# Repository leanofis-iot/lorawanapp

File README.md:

# mobileapp

## Run

In the project directory, run the [Tabris CLI](https://www.npmjs.com/package/tabris-cli) command:

```
tabris serve
```

This will start a JavaScript app code server at a free port and print its URL to the console.

The JavaScript app code can be [side-loaded](https://tabrisjs.com/documentation/2.0/developer-app.html#the-developer-console) in the [developer app](https://tabrisjs.com/documentation/2.0/developer-app.html) if the default config.xml was not changed. Otherwise, the JavaScript app code must be side-loaded in a [debug build](https://tabrisjs.com/documentation/2.0/build.html#building-a-tabrisjs-app) of this app.

## Build

The app can be built using the online build service at [tabrisjs.com](https://tabrisjs.com) or locally using [Tabris.js CLI](https://www.npmjs.com/package/tabris-cli).

See [Building a Tabris.js App](https://tabrisjs.com/documentation/2.0/build.html) for more information.

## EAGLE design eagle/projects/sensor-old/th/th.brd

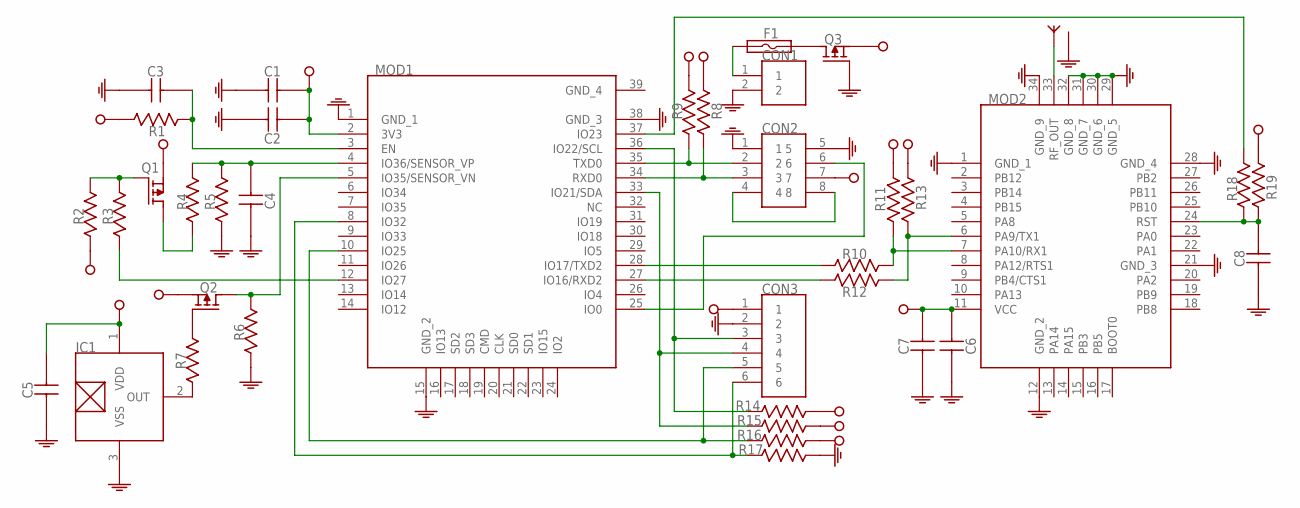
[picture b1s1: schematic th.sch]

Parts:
ANT1: SMA-RF
C1, C6: CAPACITOR-0805; 0805
C2, C3, C4, C5, C7, C8: CAPACITOR-0603; 0603
CON1: JST-PH-2-2.0MM
CON2: HEADER-8P-2R-DIP-2_0MM
CON3: CON-6P-3_81-PLUG
F1: FUSE-0805; 0805
IC1: S-5712-SOT23-3; SOT23-3
MOD1: ESP32-WROOM-32D
MOD2: RAK811
Q1, Q2, Q3: P-MOSFET; SOT23-3
R1, R2, R3, R4, R5, R6, R7, R8, R9, R10, R11, R12, R13, R14, R15, R16, R17, R18, R19: RESISTOR-0603; 0603

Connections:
GND: ANT1.2 (GND), ANT1.3 (GND), ANT1.4 (GND), ANT1.5 (GND), C1.1, C2.1, C3.1, C4.1, C5.1, C6.1, C7.1, C8.1, CON1.2, CON2.1, CON2.5, CON3.2, IC1.3 (VSS), MOD1.1 (GND_1), MOD1.15 (GND_2), MOD1.38 (GND_3), MOD2.1 (GND_1), MOD2.12 (GND_2), MOD2.21 (GND_3), MOD2.28 (GND_4), MOD2.29 (GND_5), MOD2.30 (GND_6), MOD2.31 (GND_7), MOD2.32 (GND_8), MOD2.34 (GND_9), Q3.1 (G), R5.1, R6.1, R17.2
GND_4: MOD1.39 (GND_4)
unnamed: C3.2, MOD1.3 (EN), R1.2
unnamed: IC1.2 (OUT), R7.1
unnamed: MOD2.6 (PA9/TX1), R12.2, R13.2
unnamed: MOD2.7 (PA10/RX1), R10.2, R11.2
unnamed: Q2.1 (G), R7.2
unnamed: MOD1.28 (IO17/TXD2), R10.1
unnamed: MOD1.27 (IO16/RXD2), R12.1
unnamed: CON2.2, MOD1.35 (TXD0), R9.1
unnamed: CON2.3, MOD1.34 (RXD0), R8.1
unnamed: CON2.4, CON2.8
unnamed: CON2.6, MOD1.25 (IO0)
unnamed: CON3.4, MOD1.33 (IO21/SDA), R15.1
unnamed: CON3.3, MOD1.36 (IO22/SCL), R14.1
unnamed: CON3.5, MOD1.10 (IO25), R16.1
unnamed: CON3.6, MOD1.8 (IO32), R17.1
unnamed: Q1.3 (D), R4.1
unnamed: C4.2, MOD1.4 (IO36/SENSOR_VP), R4.2, R5.2
unnamed: Q1.1 (G), R2.2, R3.2
unnamed: MOD1.12 (IO27), R3.1
unnamed: MOD1.5 (IO35/SENSOR_VN), Q2.3 (D), R6.2
unnamed: ANT1.1 (ANT), MOD2.33 (RF_OUT)
unnamed: C8.2, MOD2.24 (RST), R18.1, R19.1
unnamed: MOD1.37 (IO23), R18.2
unnamed: F1.2, Q3.3 (D)
unnamed: CON1.1, F1.1
VCC: C1.2, C2.2, C5.2, C6.2, C7.2, CON2.7, CON3.1, IC1.1 (VDD), MOD1.2 (3V3), MOD2.11 (VCC), Q1.2 (S), Q2.2 (S), Q3.2 (S), R1.1, R2.1, R8.2, R9.2, R11.1, R13.1, R14.2, R15.2, R16.2, R19.2

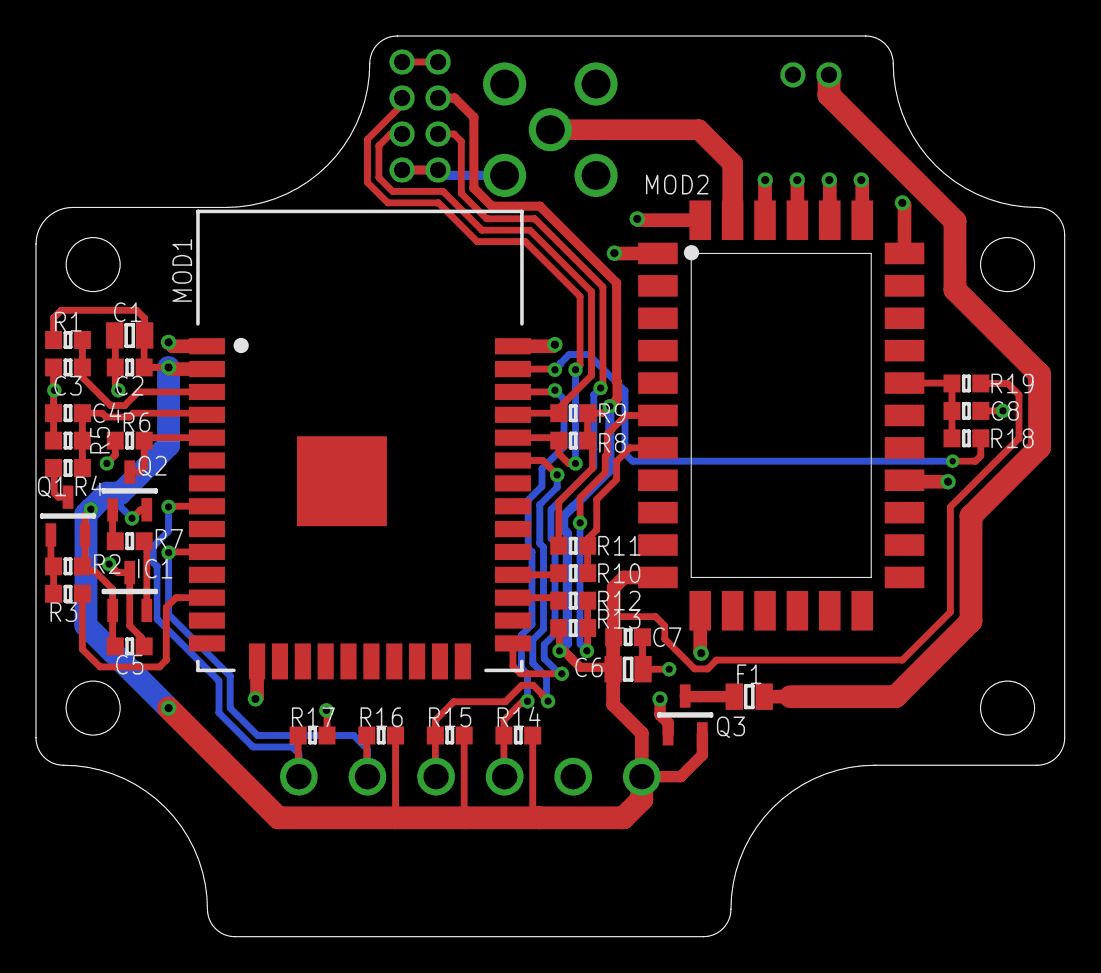
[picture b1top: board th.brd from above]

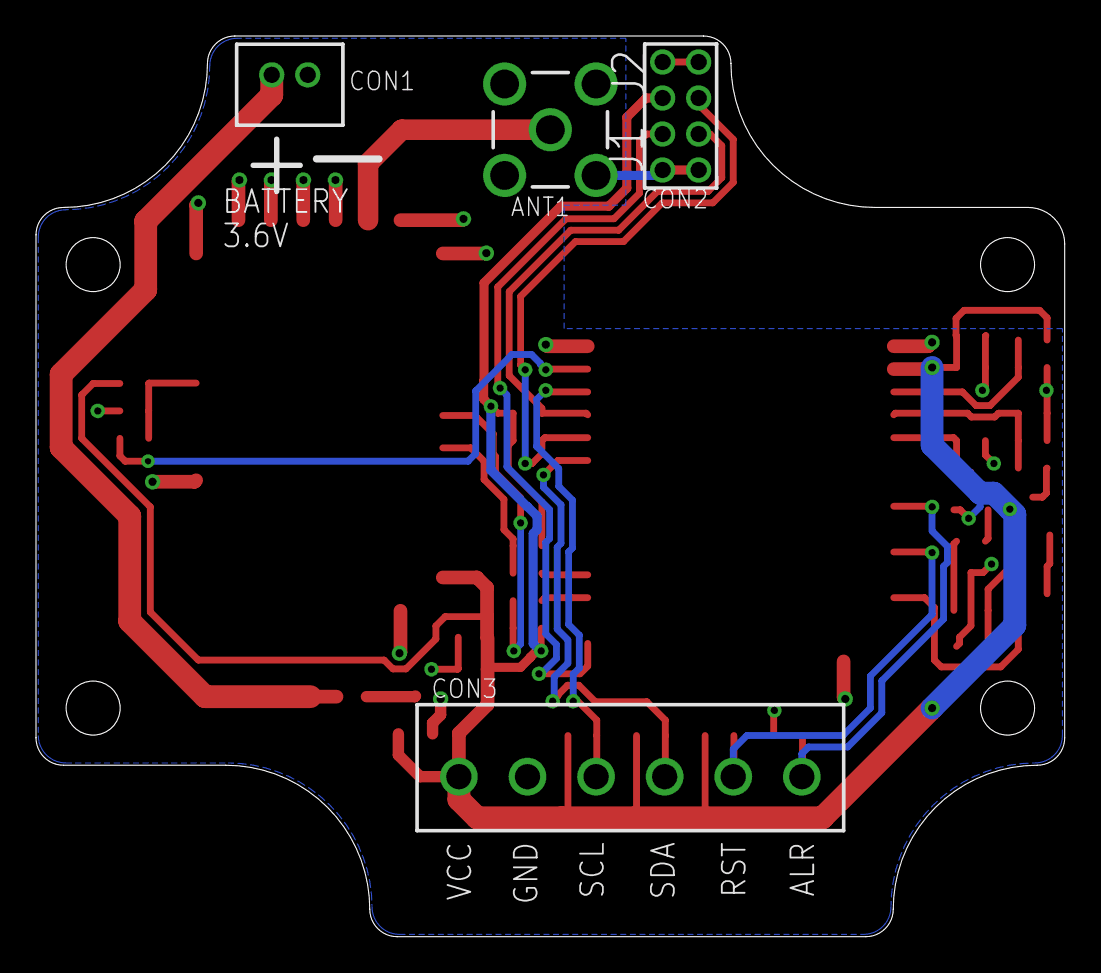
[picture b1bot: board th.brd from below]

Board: 2 copper layers, 57.1 x 50.0 mm, 38 parts (4 on the bottom side), 27 nets.

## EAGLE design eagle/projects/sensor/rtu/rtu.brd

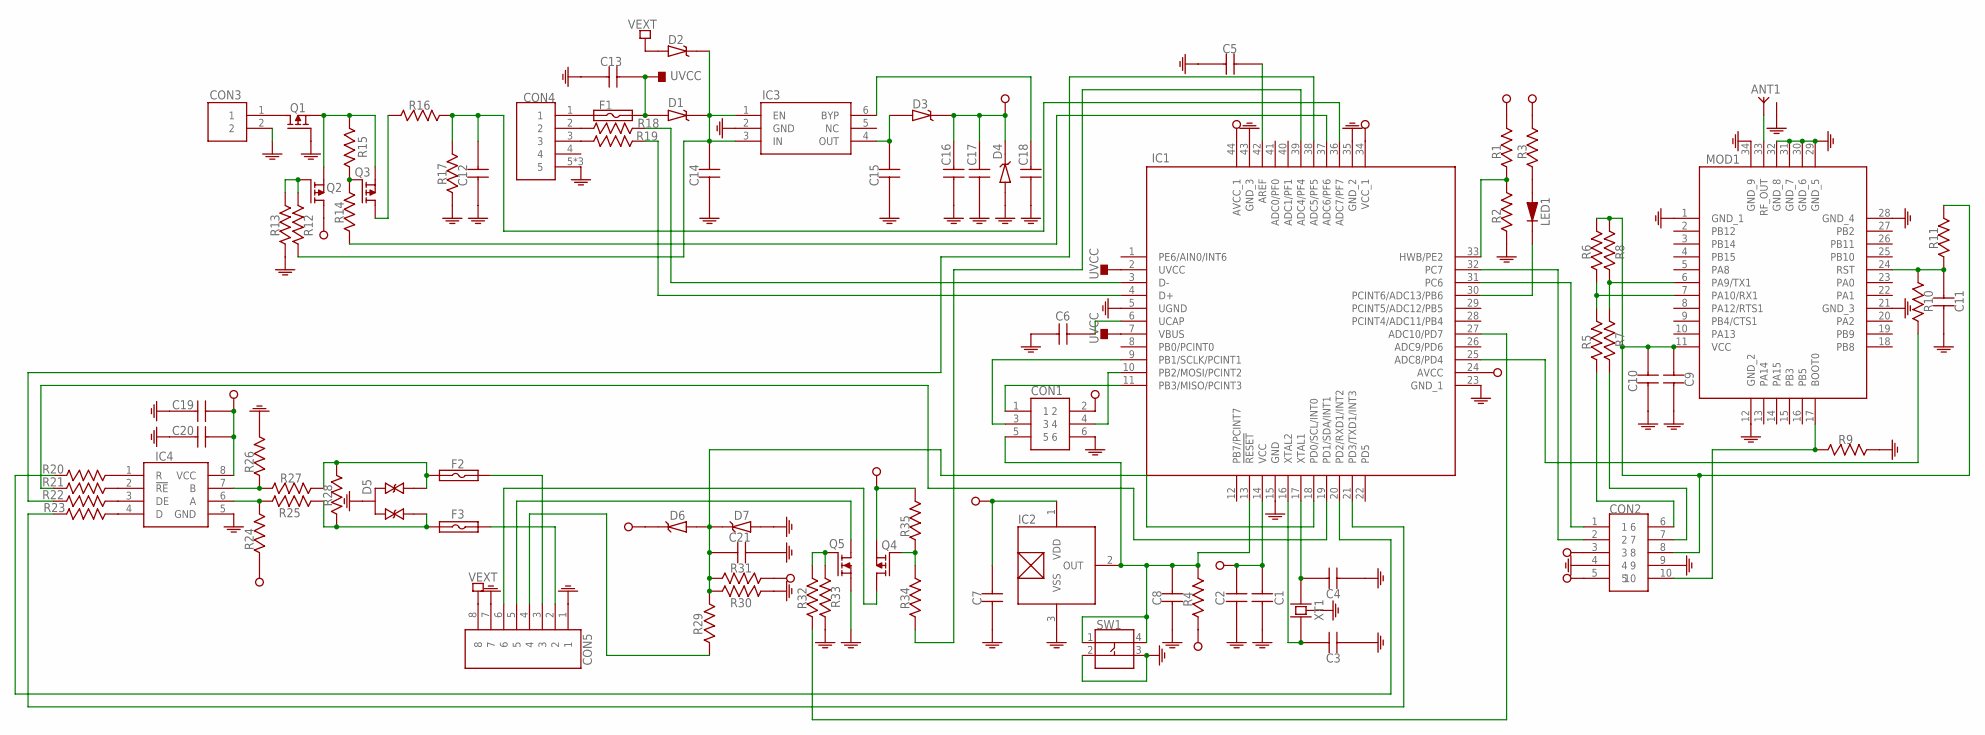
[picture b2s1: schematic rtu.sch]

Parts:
ANT1: SMA-RF
C1, C2, C3, C4, C5, C6, C7, C8, C9, C10, C11, C12, C13, C16, C17, C18, C19, C20, C21: CAPACITOR-0603; 0603
C14, C15: CAPACITOR-0805; 0805
CON1: ISP
CON2: HEADER-10P-2R-DIP-2_54MM
CON3: JST-PH-2-2.0MM
CON4: USB-MICRO-DIP-VER
CON5: CON-3_50MM-8P-1985250
D1, D2, D3: DIODE-SCHOTTKY; SOD123-DIODE
D4, D6, D7: ZENER-SOD123; SOD123-DIODE
D5: TVS-DIODE-3P; SOT23-3
F1: FUSE-0805; 0805
F2, F3: FUSE-1206; 1206
IC1: ATMEGA32U4-MU; QFN-44
IC2: S-5712-SOT23-3; SOT23-3
IC3: MIC5219-VDFN-6; VDFN-6
IC4: SN65HVD72DRB; VSON-8
LED1: LED-0603
MOD1: RAK811
Q1, Q2, Q3, Q4: P-MOSFET; SOT23-3
Q5: N-MOSFET; SOT23-3
R1, R2, R3, R4, R5, R6, R7, R8, R9, R10, R11, R12, R13, R14, R15, R16, R17, R18, R19, R20, R21, R22, R23, R24, R26, R32, R33, R34, R35: RESISTOR-0603; 0603
R25, R27: RESISTOR-0805; 0805
R28, R29, R30, R31: RESISTOR-JMP-2_54MM; HEADER-2P-DIP-2_54MM
SW1: BUTTON-4P-SMD-5X5
XT1: CRYSTAL-5032-4P

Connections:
GND: ANT1.2 (GND), ANT1.3 (GND), ANT1.4 (GND), ANT1.5 (GND), C1.1, C2.1, C3.1, C4.1, C5.1, C6.1, C7.1, C8.1, C9.1, C10.1, C11.1, C12.1, C13.1, C14.1, C15.1, C16.1, C17.1, C18.1, C19.1, C20.1, C21.2, CON1.6, CON2.4, CON2.9, CON3.2, CON4.5, CON4.6 (5), CON4.7 (5), CON5.1, CON5.7, D4.2 (A), D5.3, D7.2 (A), IC1.5 (UGND), IC1.15 (GND), IC1.23 (GND_1), IC1.35 (GND_2), IC1.43 (GND_3), IC2.3 (VSS), IC3.2 (GND), IC4.5 (GND), MOD1.1 (GND_1), MOD1.12 (GND_2), MOD1.21 (GND_3), MOD1.28 (GND_4), MOD1.29 (GND_5), MOD1.30 (GND_6), MOD1.31 (GND_7), MOD1.32 (GND_8), MOD1.34 (GND_9), Q1.1 (G), Q5.2 (S), R2.1, R9.2, R13.1, R17.1, R26.2, R30.1, R33.1, SW1.2, SW1.3, XT1.2 (GND), XT1.4 (GND)
unnamed: IC1.19 (PD1/SDA/INT1), R21.1
unnamed: C11.2, MOD1.24 (RST), R10.1, R11.1
unnamed: CON1.1, IC1.11 (PB3/MISO/PCINT3)
unnamed: ANT1.1 (ANT), MOD1.33 (RF_OUT)
unnamed: CON5.6, Q4.3 (D)
unnamed: MOD1.7 (PA10/RX1), R5.2, R6.1
unnamed: MOD1.6 (PA9/TX1), R7.2, R8.1
unnamed: IC1.27 (ADC10/PD7), R32.1
unnamed: CON1.4, IC1.10 (PB2/MOSI/PCINT2)
unnamed: C3.2, IC1.16 (XTAL2), XT1.1
unnamed: CON5.4, R29.1
unnamed: C4.2, IC1.17 (XTAL1), XT1.3 (2)
unnamed: C9.2, C10.2, CON2.8, MOD1.11 (VCC), R6.2, R8.2, R11.2
unnamed: CON2.7, R7.1
unnamed: Q5.1 (G), R32.2, R33.2
unnamed: IC1.25 (ADC8/PD4), R10.2
unnamed: D5.1, F3.1, R25.2, R28.2
unnamed: IC1.30 (PCINT6/ADC13/PB6), LED1.1 (K)
unnamed: CON2.1, IC1.31 (PC6)
unnamed: C21.1, D6.2 (A), D7.1 (K), IC1.18 (PD0/SCL/INT0), R29.2, R30.2, R31.2
unnamed: CON2.2, IC1.32 (PC7)
unnamed: IC1.20 (PD2/RXD1/INT2), R20.1
unnamed: IC1.21 (PD3/TXD1/INT3), R23.1
unnamed: IC4.7 (B), R26.1, R27.1
unnamed: IC4.6 (A), R24.2, R25.1
unnamed: CON5.3, F2.2
unnamed: CON5.5, Q5.3 (D)
unnamed: D5.2, F2.1, R27.2, R28.1
unnamed: C5.2, IC1.42 (AREF)
unnamed: Q3.1 (G), R14.2, R15.2
unnamed: CON4.1, F1.1
unnamed: C6.2, IC1.6 (UCAP)
unnamed: LED1.2 (A), R3.1
unnamed: C12.2, IC1.36 (ADC7/PF7), R16.2, R17.2
unnamed: C18.2, IC3.6 (BYP)
unnamed: C14.2, D1.1 (K), D2.1 (K), IC3.1 (EN), IC3.3 (IN), R12.1
unnamed: C15.2, D3.2 (A), IC3.4 (OUT)
unnamed: CON4.2, R18.1
unnamed: CON4.3, R19.1
unnamed: IC1.3 (D-), R18.2
unnamed: IC1.4 (D+), R19.2
unnamed: CON1.3, IC1.9 (PB1/SCLK/PCINT1)
unnamed: Q4.1 (G), R34.2, R35.1
unnamed: IC1.37 (ADC6/PF6), R14.1
unnamed: IC4.1 (R), R20.2
unnamed: IC1.38 (ADC5/PF5), R22.1
unnamed: IC1.39 (ADC4/PF4), R34.1
unnamed: IC4.2 (!RE), R21.2
unnamed: Q2.1 (G), R12.2, R13.2
unnamed: IC4.3 (DE), R22.2
unnamed: CON3.1, Q1.3 (D)
unnamed: IC4.4 (D), R23.2
unnamed: CON5.2, F3.2
unnamed: Q1.2 (S), Q2.2 (S), Q3.2 (S), R15.1
unnamed: Q3.3 (D), R16.1
unnamed: CON2.6, R5.1
unnamed: IC1.33 (HWB/PE2), R1.1, R2.2
unnamed: CON2.10, MOD1.17 (BOOT0), R9.1
unnamed: C8.2, CON1.5, IC1.13 (!RESET), IC2.2 (OUT), R4.2, SW1.1, SW1.4
UVCC: C13.2, D1.2 (A), F1.2, IC1.2 (UVCC), IC1.7 (VBUS)
VCC: C1.2, C2.2, C7.2, C16.2, C17.2, C19.2, C20.2, CON1.2, CON2.3, CON2.5, D3.1 (K), D4.1 (K), D6.1 (K), IC1.14 (VCC), IC1.24 (AVCC), IC1.34 (VCC_1), IC1.44 (AVCC_1), IC2.1 (VDD), IC4.8 (VCC), Q2.3 (D), Q4.2 (S), R1.2, R3.2, R4.1, R24.1, R31.1, R35.2
VEXT: CON5.8, D2.2 (A)

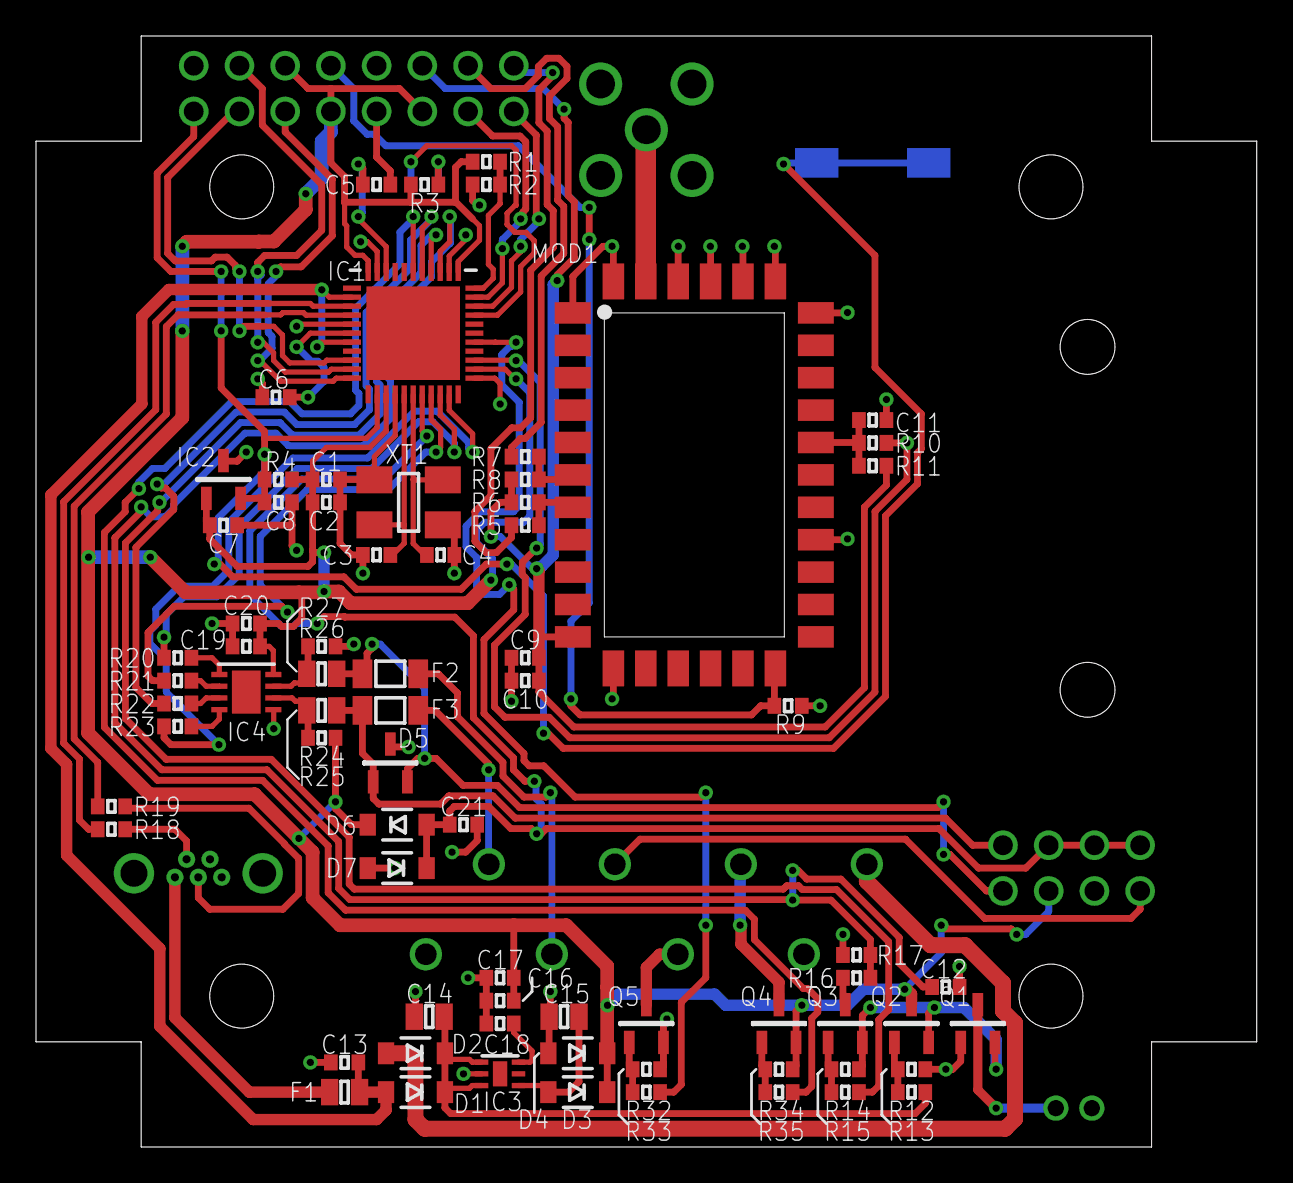
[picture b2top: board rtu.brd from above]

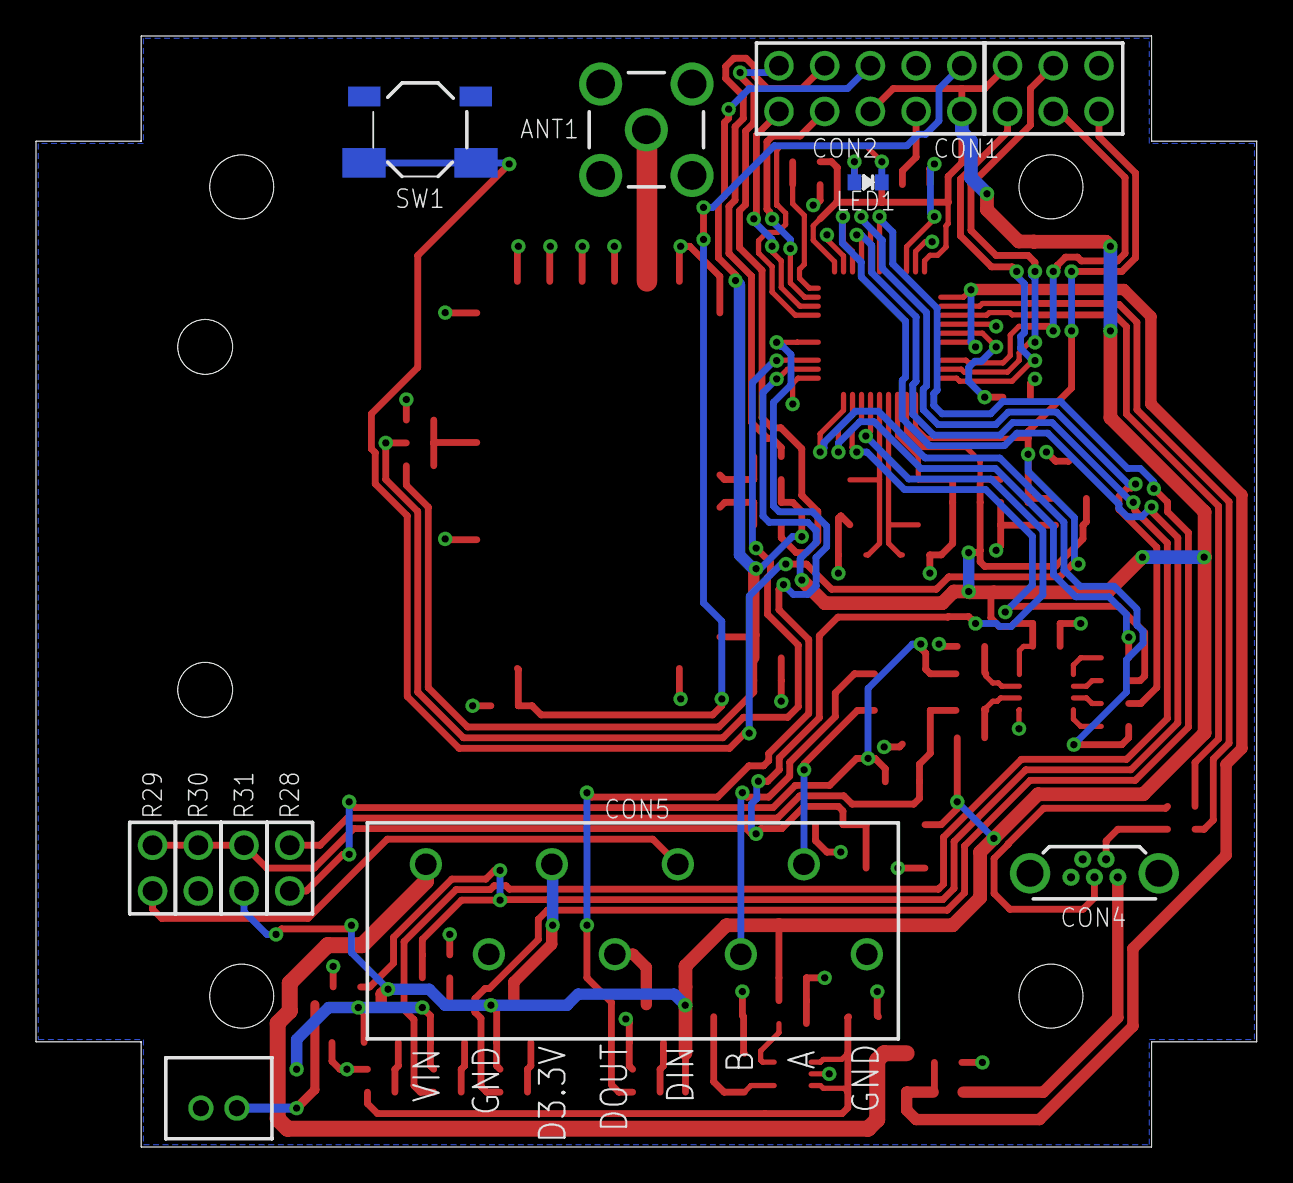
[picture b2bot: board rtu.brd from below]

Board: 2 copper layers, 67.8 x 61.7 mm, 85 parts (12 on the bottom side), 63 nets.

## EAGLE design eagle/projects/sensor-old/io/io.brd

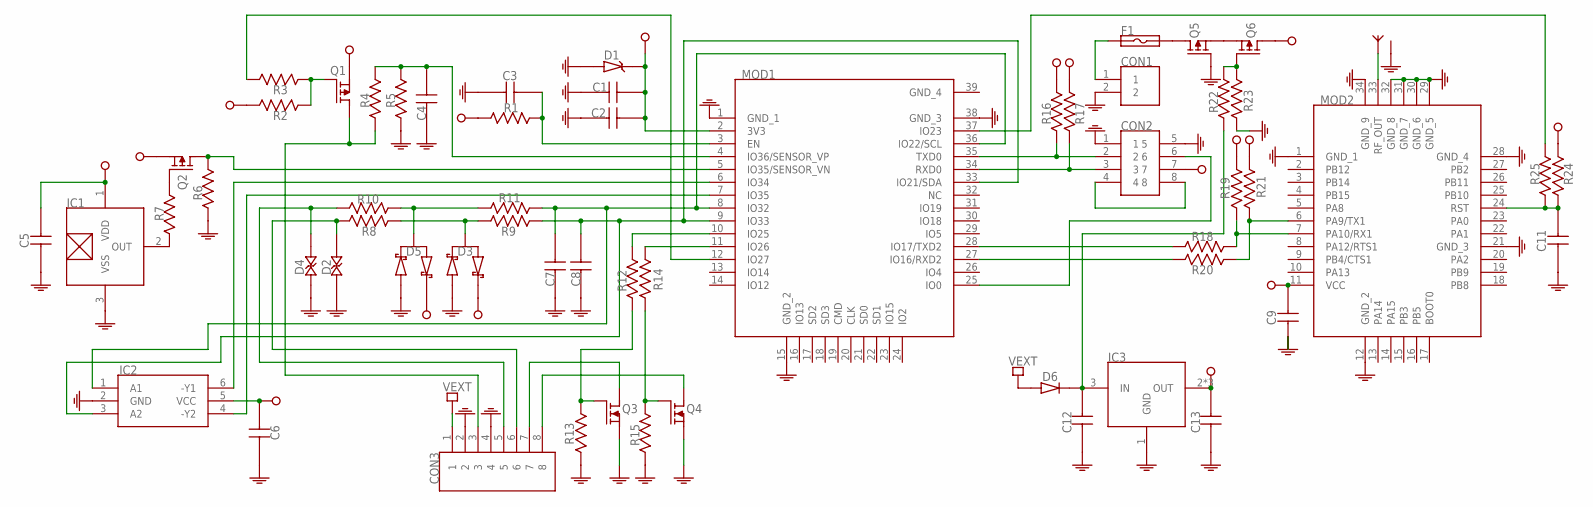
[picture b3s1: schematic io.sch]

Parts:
ANT1: SMA-RF
C1, C12, C13: CAPACITOR-0805; 0805
C2, C3, C4, C5, C6, C7, C8, C9, C11: CAPACITOR-0603; 0603
CON1: JST-PH-2-2.0MM
CON2: HEADER-8P-2R-DIP-2_0MM
CON3: CON-89-3_81-PLUG; CON-8P-3_81-PLUG
D1: ZENER-SOD123; SOD123-DIODE
D2, D4: TVS-DIODE-SMA; DO-214AC-SMA
D3, D5: SCHOTTKY-SERIE-3P; SOT23-3
D6: DIODE-DO-214AC-SMA; DO-214AC-SMA-DIODE
F1: FUSE-0805; 0805
IC1: S-5712-SOT23-3; SOT23-3
IC2: NL27WZ04DTT1G; SOT23-6
IC3: VREG-SOT-223; SOT-223
MOD1: ESP32-WROOM-32D
MOD2: RAK811
Q1, Q2, Q5, Q6: P-MOSFET; SOT23-3
Q3, Q4: N-MOSFET; SOT23-3
R1, R2, R3, R4, R5, R6, R7, R9, R11, R12, R13, R14, R15, R16, R17, R18, R19, R20, R21, R22, R23, R24, R25: RESISTOR-0603; 0603
R8, R10: RESISTOR-0805; 0805

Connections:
GND: ANT1.2 (GND), ANT1.3 (GND), ANT1.4 (GND), ANT1.5 (GND), C1.1, C2.1, C3.1, C4.1, C5.1, C6.2, C7.1, C8.1, C9.1, C11.1, C12.1, C13.1, CON1.2, CON2.1, CON2.5, CON3.2, CON3.4, D1.2 (A), D2.1, D3.1, D4.1, D5.1, IC1.3 (VSS), IC2.2 (GND), IC3.1 (GND), MOD1.1 (GND_1), MOD1.15 (GND_2), MOD1.38 (GND_3), MOD2.1 (GND_1), MOD2.12 (GND_2), MOD2.21 (GND_3), MOD2.28 (GND_4), MOD2.29 (GND_5), MOD2.30 (GND_6), MOD2.31 (GND_7), MOD2.32 (GND_8), MOD2.34 (GND_9), Q3.2 (S), Q4.2 (S), Q5.1 (G), R5.1, R6.1, R13.1, R15.1, R23.1
GND_4: MOD1.39 (GND_4)
unnamed: C3.2, MOD1.3 (EN), R1.2
unnamed: ANT1.1 (ANT), MOD2.33 (RF_OUT)
unnamed: MOD2.6 (PA9/TX1), R20.2, R21.2
unnamed: MOD2.7 (PA10/RX1), R18.2, R19.2
unnamed: MOD1.37 (IO23), R25.2
unnamed: MOD1.28 (IO17/TXD2), R18.1
unnamed: MOD1.27 (IO16/RXD2), R20.1
unnamed: CON2.2, MOD1.35 (TXD0), R16.1
unnamed: CON2.3, MOD1.34 (RXD0), R17.1
unnamed: CON2.4, CON2.8
unnamed: CON2.6, MOD1.25 (IO0)
unnamed: CON1.1, F1.1
unnamed: MOD1.5 (IO35/SENSOR_VN), Q2.3 (D), R6.2
unnamed: CON3.7, Q3.3 (D)
unnamed: C7.2, IC2.1 (A1), MOD1.8 (IO32), MOD1.36 (IO22/SCL), R11.2
unnamed: CON3.3, Q1.3 (D), R4.1
unnamed: C11.2, MOD2.24 (RST), R24.1, R25.1
unnamed: Q1.1 (G), R2.1, R3.1
unnamed: F1.2, Q5.3 (D)
unnamed: C8.2, IC2.3 (A2), MOD1.9 (IO33), MOD1.33 (IO21/SDA), R9.2
unnamed: Q2.1 (G), R7.2
unnamed: IC2.4 (-Y2), MOD1.7 (IO35)
unnamed: D5.3, R10.1, R11.1
unnamed: D3.3, R8.1, R9.1
unnamed: MOD1.11 (IO26), R14.2
unnamed: MOD1.10 (IO25), R12.2
unnamed: Q4.1 (G), R14.1, R15.2
unnamed: IC2.6 (-Y1), MOD1.6 (IO34)
unnamed: CON3.8, Q4.3 (D)
unnamed: Q5.2 (S), Q6.2 (S)
unnamed: Q3.1 (G), R12.1, R13.2
unnamed: MOD1.12 (IO27), R3.2
unnamed: IC1.2 (OUT), R7.1
unnamed: C12.2, D6.1 (K), IC3.3 (IN), R22.1
unnamed: Q6.1 (G), R22.2, R23.2
unnamed: C4.2, MOD1.4 (IO36/SENSOR_VP), R4.2, R5.2
unnamed: CON3.6, D2.2, R8.2
unnamed: CON3.5, D4.2, R10.2
VCC: C1.2, C2.2, C5.2, C6.1, C9.2, C13.2, CON2.7, D1.1 (K), D3.2, D5.2, IC1.1 (VDD), IC2.5 (VCC), IC3.2 (OUT), IC3.4 (OUT), IC3.5 (OUT), MOD1.2 (3V3), MOD2.11 (VCC), Q1.2 (S), Q2.2 (S), Q6.3 (D), R1.1, R2.2, R16.2, R17.2, R19.1, R21.1, R24.2
VEXT: CON3.1, D6.2 (A)

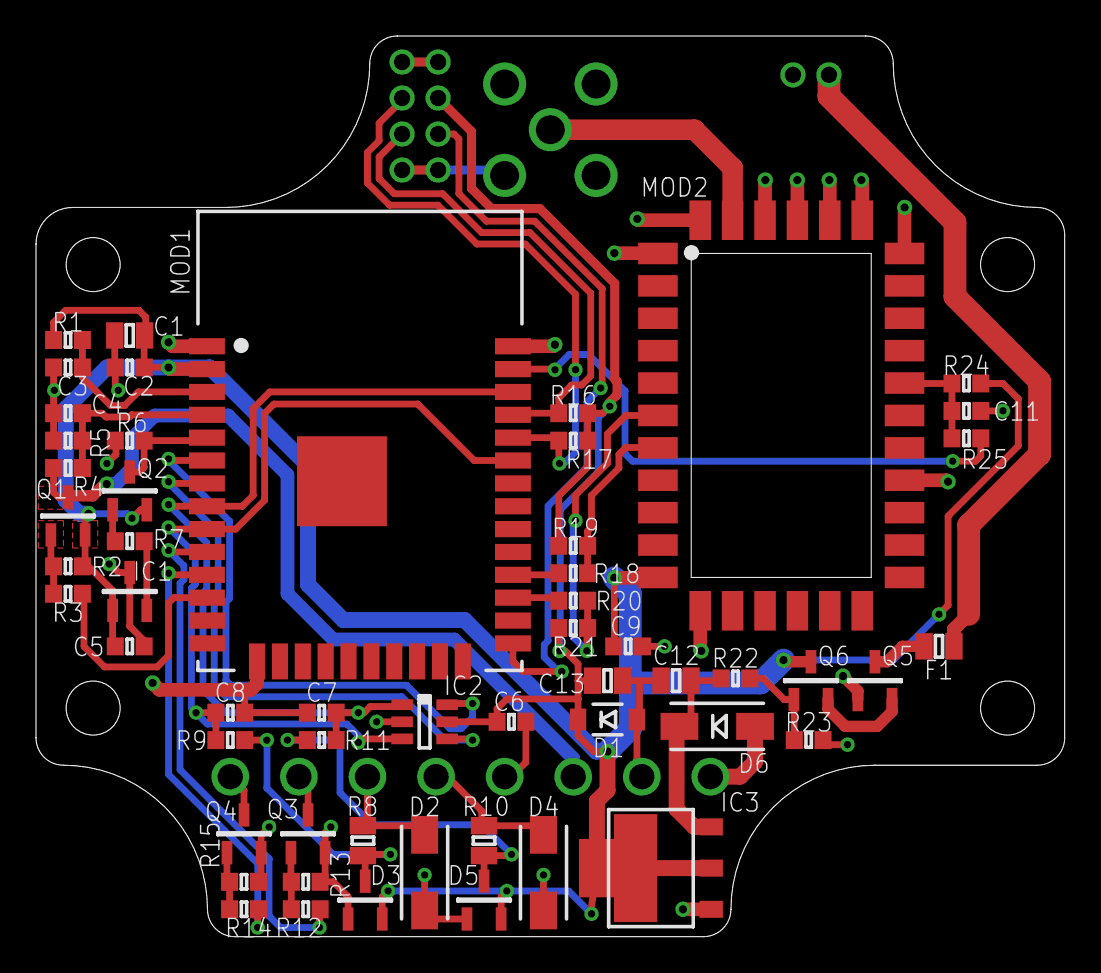
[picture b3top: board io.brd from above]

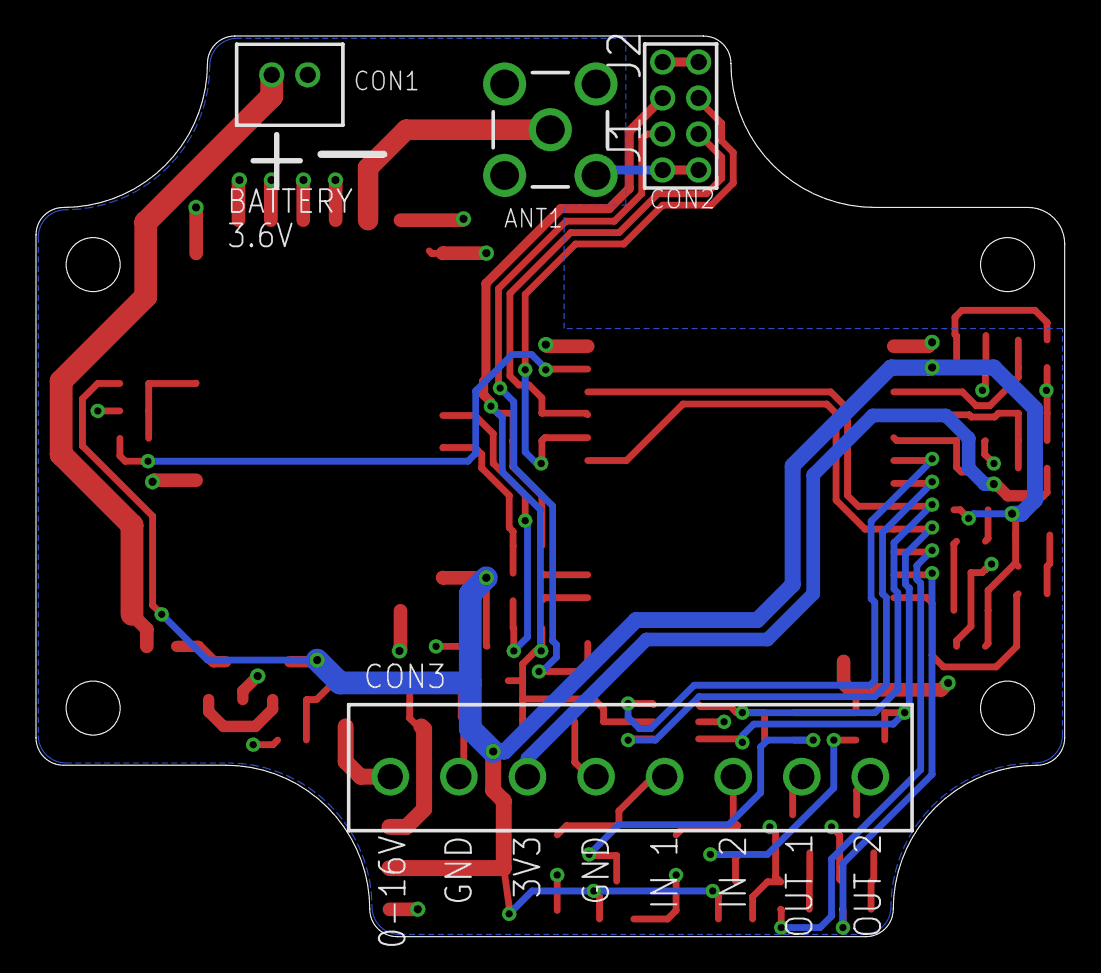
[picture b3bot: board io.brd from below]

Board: 2 copper layers, 57.1 x 50.0 mm, 59 parts (4 on the bottom side), 41 nets.

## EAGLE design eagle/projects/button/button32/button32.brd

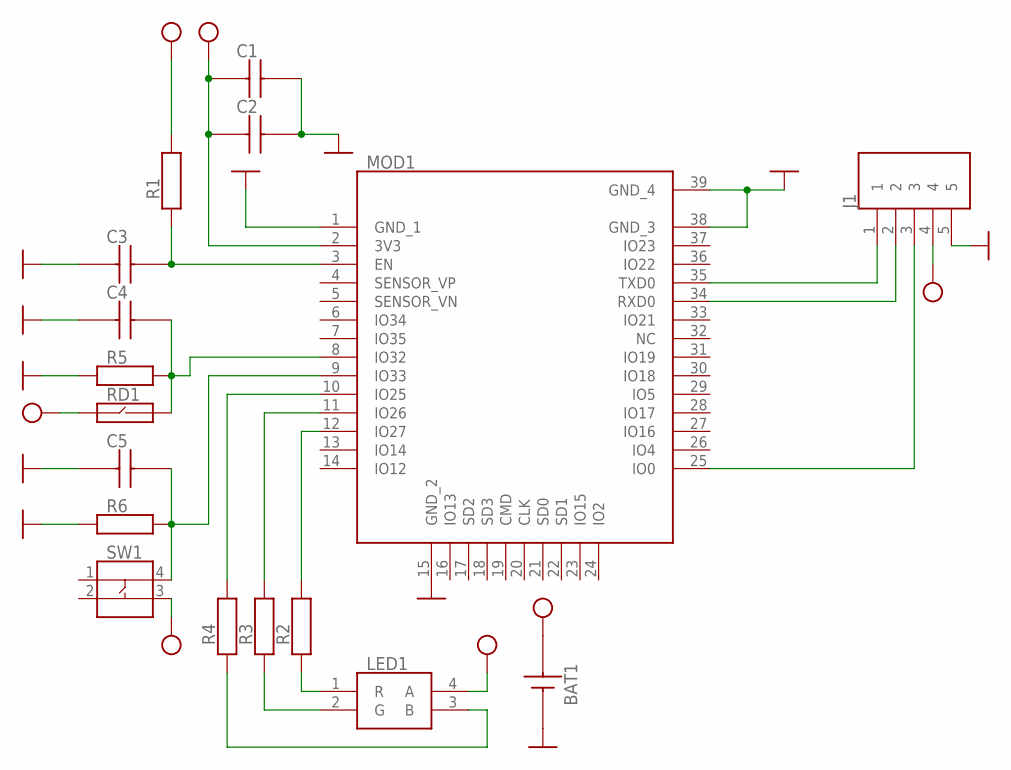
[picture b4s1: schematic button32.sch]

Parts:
BAT1: BH-411-1P24
C1, C2, C3, C4, C5: CAPACITOR-0603; 0603
J1: HEADER-5P-DıP-2_54MM
LED1: LED-RGB-3528-PLCC4
MOD1: ESP32-WROOM-32D
R1, R2, R3, R4, R5, R6: RESISTOR-0603; 0603
RD1: REED; 0603
SW1: BUTTON-4P-SMD-5X5

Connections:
GND: BAT1.2 (-), C1.2, C2.2, C3.1, C4.1, C5.1, J1.5, MOD1.1 (GND_1), MOD1.15 (GND_2), MOD1.38 (GND_3), MOD1.39 (GND_4), R5.1, R6.1
unnamed: C3.2, MOD1.3 (EN), R1.1
unnamed: J1.1, MOD1.35 (TXD0)
unnamed: J1.2, MOD1.34 (RXD0)
unnamed: J1.3, MOD1.25 (IO0)
unnamed: LED1.1 (R), R2.1
unnamed: LED1.2 (G), R3.1
unnamed: LED1.3 (B), R4.1
unnamed: C4.2, MOD1.8 (IO32), R5.2, RD1.2
unnamed: MOD1.12 (IO27), R2.2
unnamed: MOD1.11 (IO26), R3.2
unnamed: MOD1.10 (IO25), R4.2
unnamed: C5.2, MOD1.9 (IO33), R6.2, SW1.4
VCC: BAT1.1 (+), C1.1, C2.1, J1.4, LED1.4 (A), MOD1.2 (3V3), R1.2, RD1.1, SW1.3

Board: 2 copper layers, 17 parts (0 on the bottom side), 14 nets, no tracks yet.

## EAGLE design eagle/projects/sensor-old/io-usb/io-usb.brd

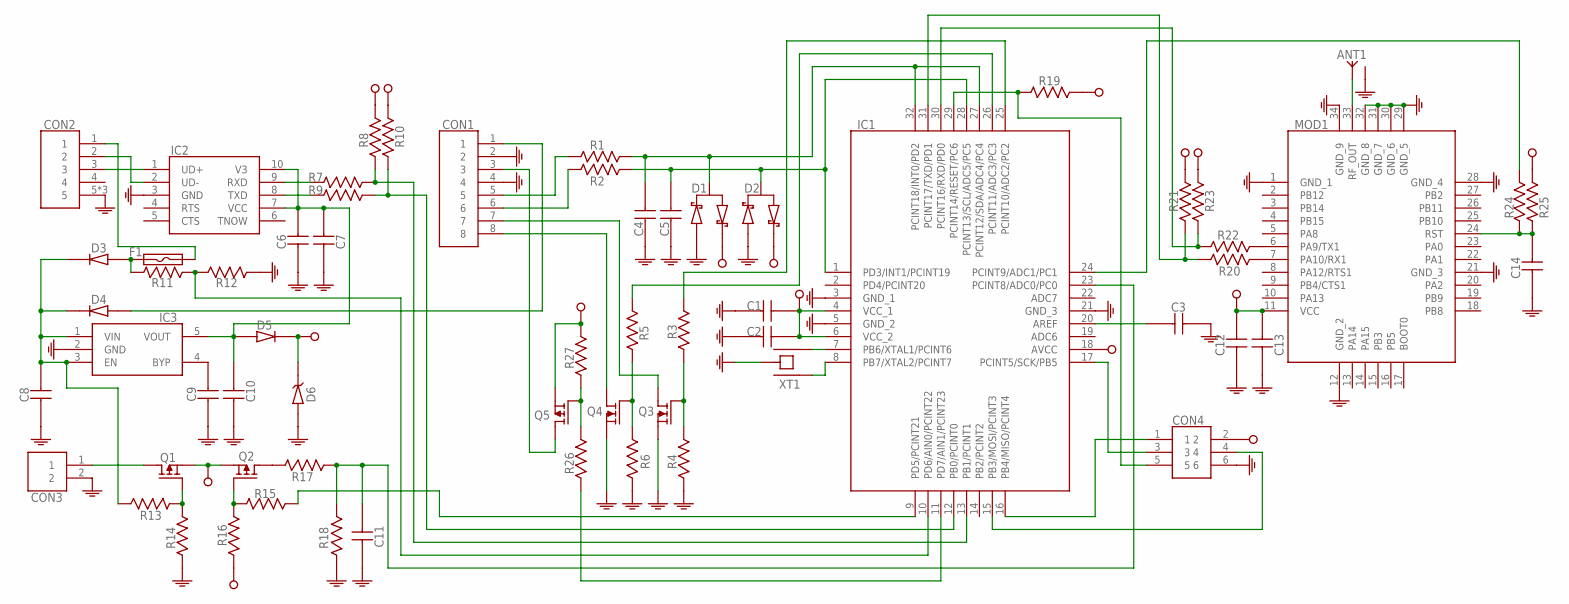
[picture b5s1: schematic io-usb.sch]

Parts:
ANT1: SMA-RF
C1, C6, C8, C10, C13: CAPACITOR-0805; 0805
C2, C3, C4, C5, C7, C9, C11, C12, C14: CAPACITOR-0603; 0603
CON1: CON-89-3_81-PLUG; CON-8P-3_81-PLUG
CON2: USB-MICRO-DIP-VER
CON3: JST-PH-2-2.0MM
CON4: ISP
D1, D2: SCHOTTKY-SERIE-3P; SOT23-3
D3, D4, D5: DIODE-SOD123; SOD123-DIODE
D6: ZENER-SOD123; SOD123-DIODE
F1: FUSE-0805; 0805
IC1: ATMEGA328P-AU; TQFP-32
IC2: CH340E; MSOP-10
IC3: MIC5219; SOT23-5
MOD1: RAK811
Q1, Q2, Q5: P-MOSFET; SOT23-3
Q3, Q4: N-MOSFET; SOT23-3
R1, R2: RESISTOR-0805; 0805
R3, R4, R5, R6, R7, R8, R9, R10, R11, R12, R13, R14, R15, R16, R17, R18, R19, R20, R21, R22, R23, R24, R25, R26, R27: RESISTOR-0603; 0603
XT1: RESONATOR-3215

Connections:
GND: ANT1.2 (GND), ANT1.3 (GND), ANT1.4 (GND), ANT1.5 (GND), C1.1, C2.1, C3.2, C4.1, C5.1, C6.1, C7.1, C8.1, C9.2, C10.1, C11.1, C12.1, C13.1, C14.1, CON1.2, CON1.4, CON2.5, CON2.6 (5), CON2.7 (5), CON3.2, CON4.6, D1.1, D2.1, D6.2 (A), IC1.3 (GND_1), IC1.5 (GND_2), IC1.21 (GND_3), IC2.3 (GND), IC3.2 (GND), MOD1.1 (GND_1), MOD1.12 (GND_2), MOD1.21 (GND_3), MOD1.28 (GND_4), MOD1.29 (GND_5), MOD1.30 (GND_6), MOD1.31 (GND_7), MOD1.32 (GND_8), MOD1.34 (GND_9), Q3.2 (S), Q4.2 (S), R4.1, R6.1, R12.1, R14.1, R18.1, XT1.3
unnamed: D3.2 (A), F1.2, R11.1
unnamed: C9.1, IC3.4 (BYP)
unnamed: IC2.9 (RXD), R7.1
unnamed: IC2.8 (TXD), R9.1
unnamed: CON2.3, IC2.1 (UD+)
unnamed: CON2.2, IC2.2 (UD-)
unnamed: CON3.1, Q1.3 (D)
unnamed: IC1.7 (PB6/XTAL1/PCINT6), XT1.1
unnamed: CON2.1, F1.1
unnamed: IC1.8 (PB7/XTAL2/PCINT7), XT1.2
unnamed: IC1.9 (PD5/PCINT21), R15.2
unnamed: C8.2, D3.1 (K), D4.1 (K), IC3.1 (VIN), IC3.3 (EN), R13.2
unnamed: Q2.1 (G), R15.1, R16.2
unnamed: C11.2, IC1.23 (PCINT8/ADC0/PC0), R17.2, R18.2
unnamed: CON1.1, D4.2 (A)
unnamed: ANT1.1 (ANT), MOD1.33 (RF_OUT)
unnamed: MOD1.6 (PA9/TX1), R22.2
unnamed: MOD1.7 (PA10/RX1), R20.2
unnamed: C14.2, MOD1.24 (RST), R24.1, R25.1
unnamed: IC1.30 (PCINT16/RXD/PD0), R22.1, R23.1
unnamed: IC1.31 (PCINT17/TXD/PD1), R20.1, R21.1
unnamed: CON4.5, IC1.29 (PCINT14/RESET/PC6), R19.1
unnamed: IC1.13 (PB1/PCINT1), R7.2, R8.1
unnamed: C4.2, D1.3, IC1.27 (PCINT12/SDA/ADC4/PC4), IC1.32 (PCINT18/INT0/PD2), R1.2
unnamed: IC1.12 (PB0/PCINT0), R9.2, R10.1
unnamed: CON1.6, R2.1
unnamed: C5.2, D2.3, IC1.1 (PD3/INT1/PCINT19), IC1.28 (PCINT13/SCL/ADC5/PC5), R2.2
unnamed: CON1.5, R1.1
unnamed: Q4.1 (G), R5.1, R6.2
unnamed: Q3.1 (G), R3.1, R4.2
unnamed: IC1.26 (PCINT11/ADC3/PC3), R5.2
unnamed: IC1.25 (PCINT10/ADC2/PC2), R3.2
unnamed: CON1.7, Q3.3 (D)
unnamed: CON1.8, Q4.3 (D)
unnamed: IC1.24 (PCINT9/ADC1/PC1), R24.2
unnamed: Q1.1 (G), R13.1, R14.2
unnamed: Q2.3 (D), R17.1
unnamed: IC1.10 (PD6/AIN0/PCINT22), R11.2, R12.2
unnamed: CON4.3, IC1.17 (PCINT5/SCK/PB5)
unnamed: CON4.1, IC1.16 (PB4/MISO/PCINT4)
unnamed: CON4.4, IC1.15 (PB3/MOSI/PCINT3)
unnamed: C3.1, IC1.20 (AREF)
unnamed: Q5.1 (G), R26.2, R27.1
unnamed: CON1.3, Q5.3 (D)
unnamed: IC1.11 (PD7/AIN1/PCINT23), R26.1
unnamed: C6.2, C7.2, C10.2, D5.2 (A), IC2.7 (VCC), IC2.10 (V3), IC3.5 (VOUT)
PD4/PCINT20: IC1.2 (PD4/PCINT20)
VCC: C1.2, C2.2, C12.2, C13.2, CON4.2, D1.2, D2.2, D5.1 (K), D6.1 (K), IC1.4 (VCC_1), IC1.6 (VCC_2), IC1.18 (AVCC), MOD1.11 (VCC), Q1.2 (S), Q2.2 (S), Q5.2 (S), R8.2, R10.2, R16.1, R19.2, R21.2, R23.2, R25.2, R27.2

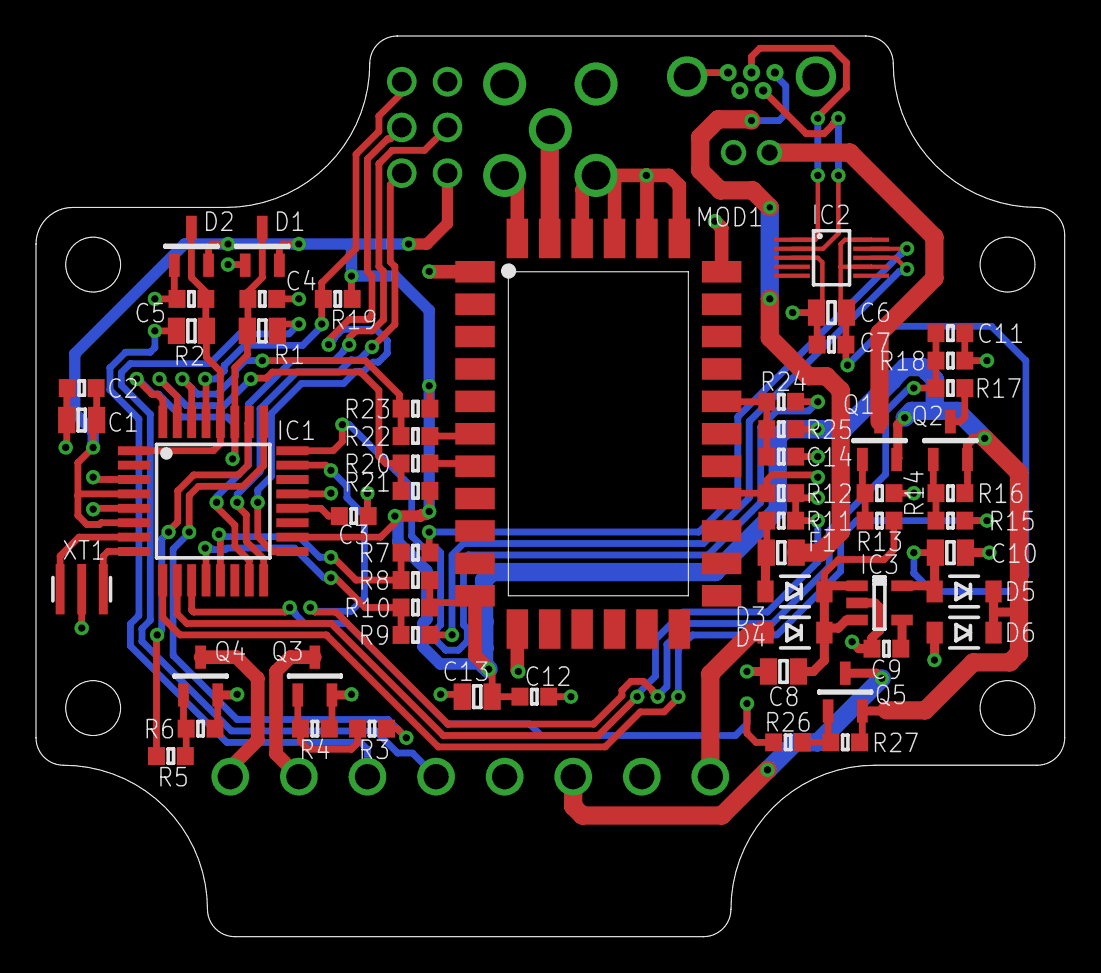
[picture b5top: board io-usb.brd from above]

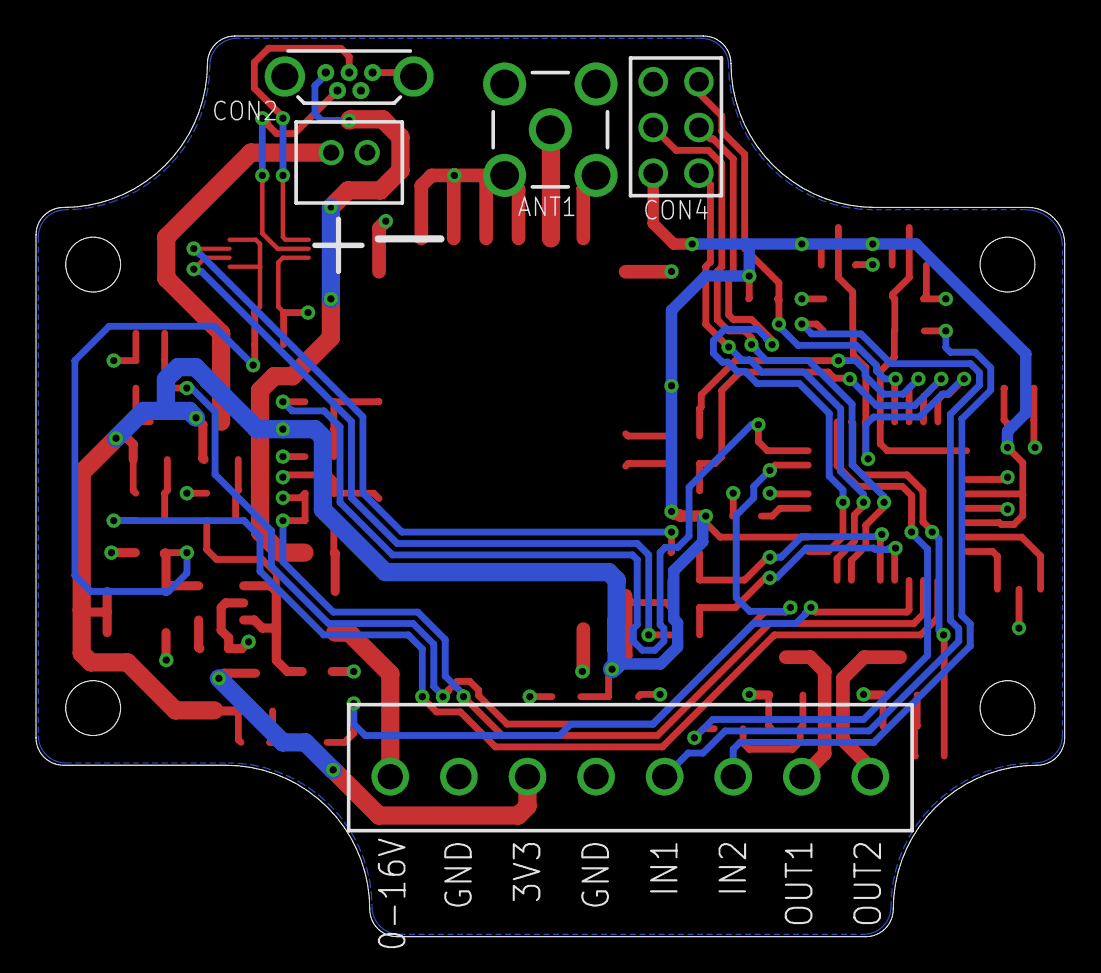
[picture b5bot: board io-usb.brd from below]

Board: 2 copper layers, 57.1 x 50.0 mm, 63 parts (5 on the bottom side), 48 nets.
